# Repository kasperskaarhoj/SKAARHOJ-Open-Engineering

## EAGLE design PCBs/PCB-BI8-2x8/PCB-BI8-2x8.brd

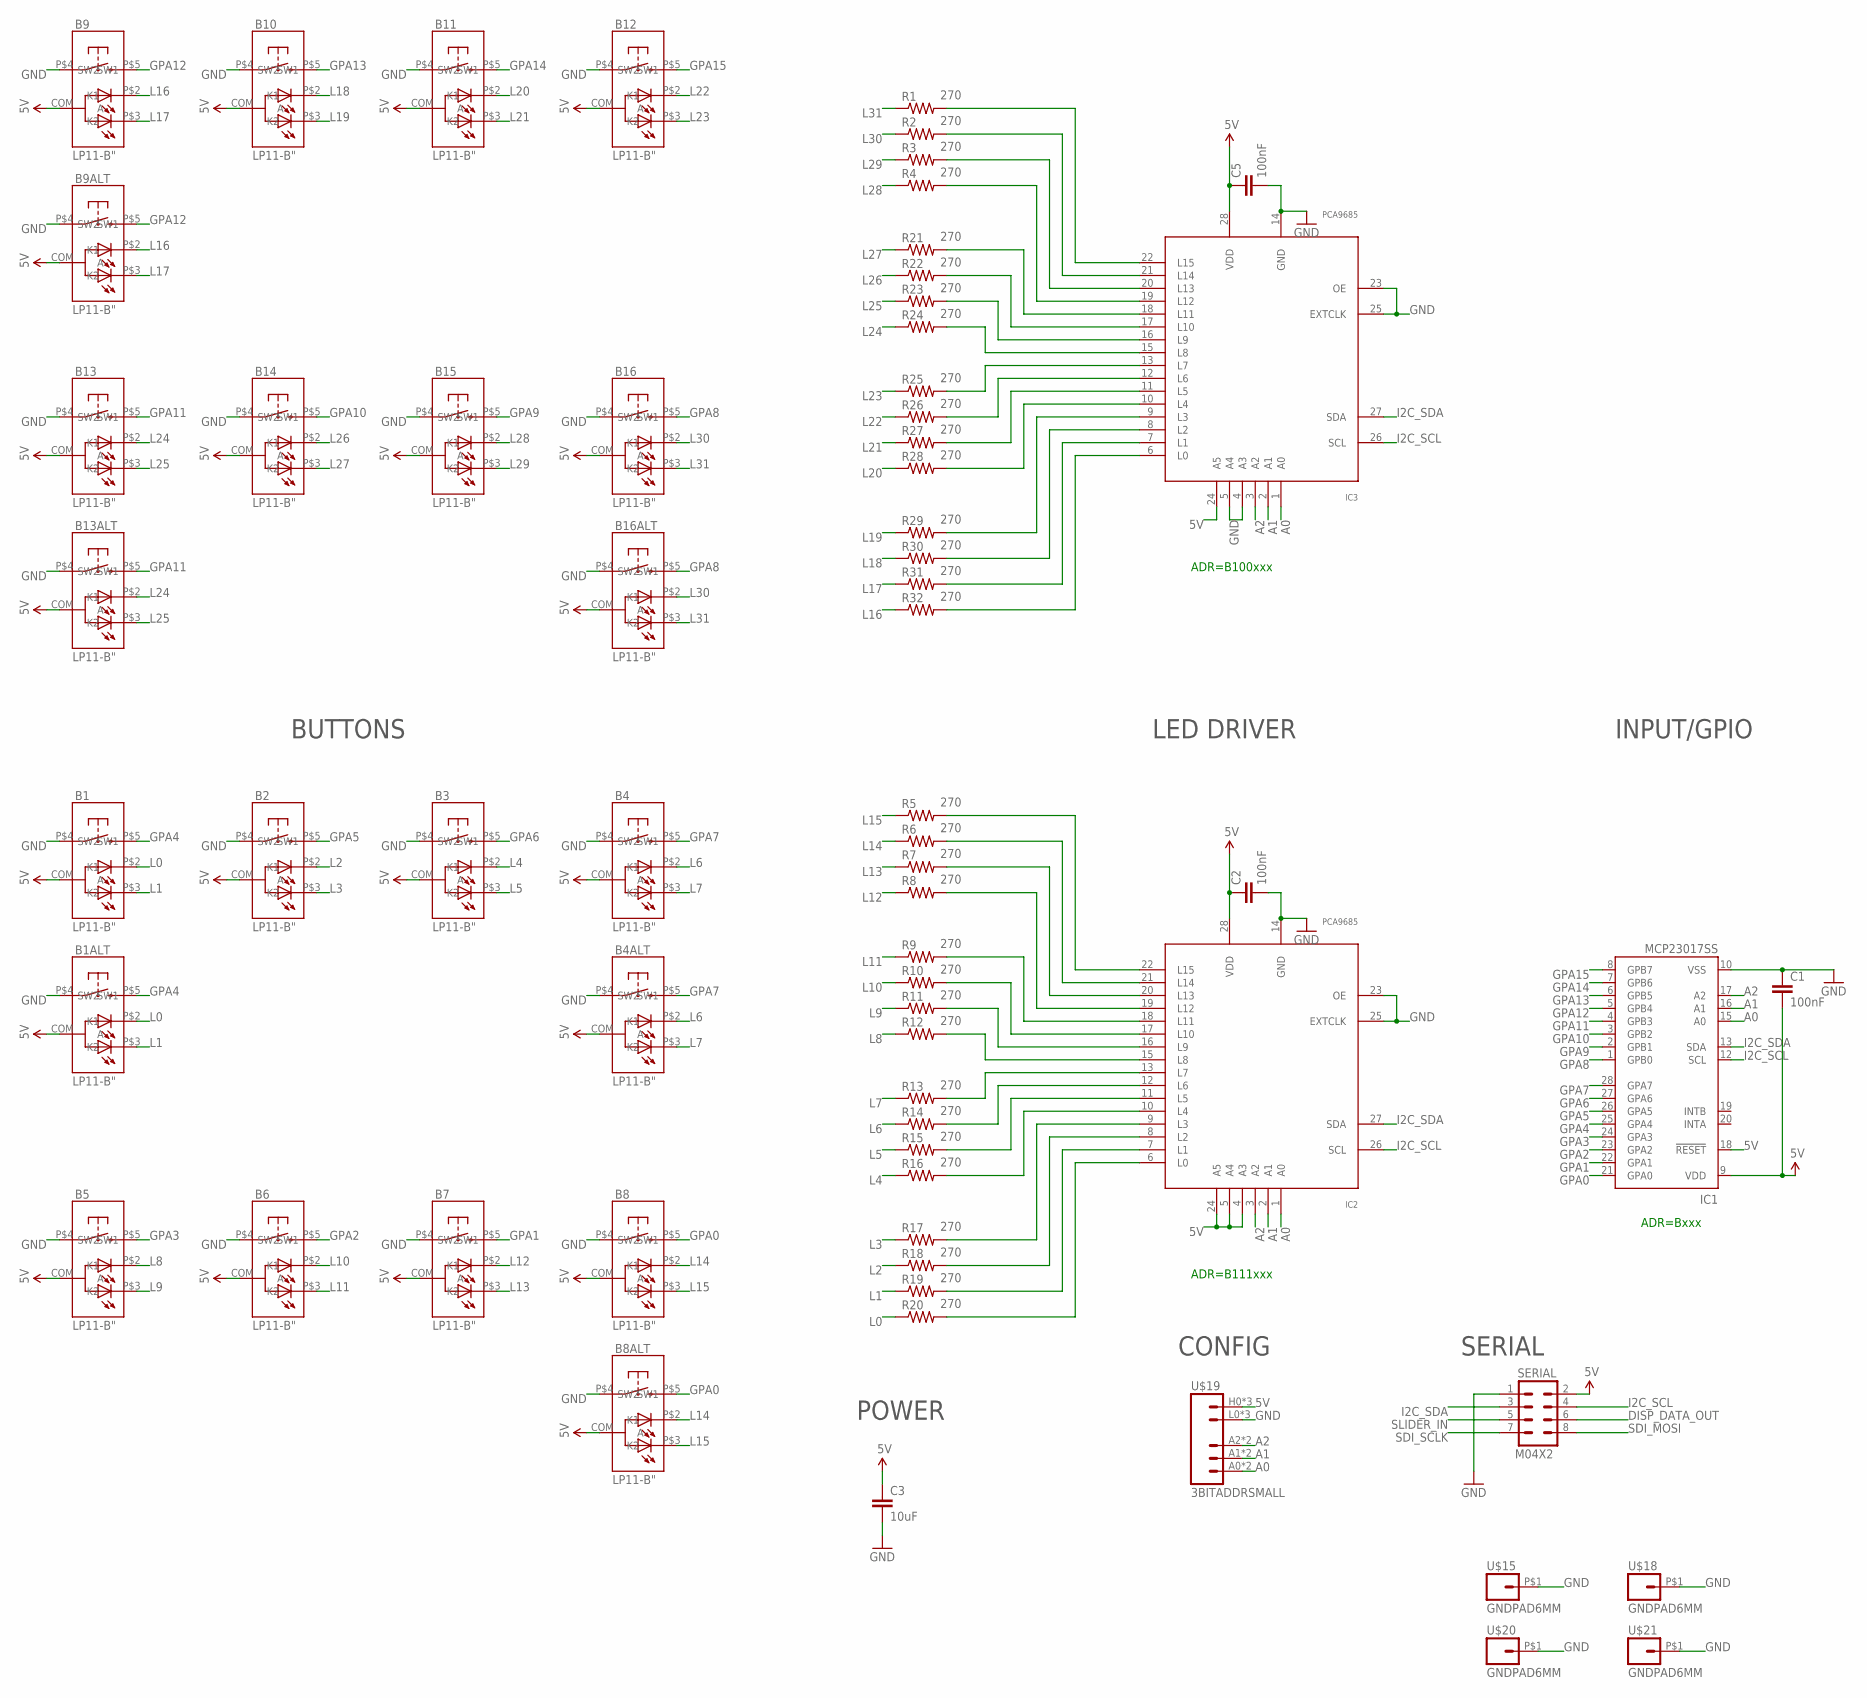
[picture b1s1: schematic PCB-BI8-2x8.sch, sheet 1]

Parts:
B1, B1ALT, B2, B3, B4, B4ALT, B5, B6, B7, B8, B8ALT, B9, B9ALT, B10, B11, B12, B13, B13ALT, B14, B15, B16, B16ALT: LP11-B"; LP11
C1, C2, C5: 100nF; 0603-CAP
C3: 10uF; 0805
IC1: MCP23017SS; SSOP28; MPN MCP23017-E/SS
IC2, IC3: PCA9685; TSSOP28
R1, R2, R3, R4, R5, R6, R7, R8, R9, R10, R11, R12, R13, R14, R15, R16, R17, R18, R19, R20, R21, R22, R23, R24, R25, R26, R27, R28, R29, R30, R31, R32: 270; 0603-RES
SERIAL: M04X2; 2X4
U$15, U$18, U$20, U$21: GNDPAD6MM; 3.2MMPAD6MM
U$19: 3BITADDRSMALL; 3BITADDR_SMALL

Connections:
5V: B1.COM (A), B1ALT.COM (A), B2.COM (A), B3.COM (A), B4.COM (A), B4ALT.COM (A), B5.COM (A), B6.COM (A), B7.COM (A), B8.COM (A), B8ALT.COM (A), B9.COM (A), B9ALT.COM (A), B10.COM (A), B11.COM (A), B12.COM (A), B13.COM (A), B13ALT.COM (A), B14.COM (A), B15.COM (A), B16.COM (A), B16ALT.COM (A), C1.2, C2.1, C3.1, C5.1, IC1.9 (VDD), IC1.18 (!RESET), IC2.4 (A3), IC2.5 (A4), IC2.24 (A5), IC2.28 (VDD), IC3.24 (A5), IC3.28 (VDD), SERIAL.2, U$19.H0 (VCC), U$19.H1 (VCC), U$19.H2 (VCC)
A0: IC1.15 (A0), IC2.1 (A0), IC3.1 (A0), U$19.A0, U$19.AS0 (A0)
A1: IC1.16 (A1), IC2.2 (A1), IC3.2 (A1), U$19.A1, U$19.AS1 (A1)
A2: IC1.17 (A2), IC2.3 (A2), IC3.3 (A2), U$19.A2, U$19.AS2 (A2)
DISP_DATA_OUT: SERIAL.6
GND: B1.P$4 (SW1), B1ALT.P$4 (SW1), B2.P$4 (SW1), B3.P$4 (SW1), B4.P$4 (SW1), B4ALT.P$4 (SW1), B5.P$4 (SW1), B6.P$4 (SW1), B7.P$4 (SW1), B8.P$4 (SW1), B8ALT.P$4 (SW1), B9.P$4 (SW1), B9ALT.P$4 (SW1), B10.P$4 (SW1), B11.P$4 (SW1), B12.P$4 (SW1), B13.P$4 (SW1), B13ALT.P$4 (SW1), B14.P$4 (SW1), B15.P$4 (SW1), B16.P$4 (SW1), B16ALT.P$4 (SW1), C1.1, C2.2, C3.2, C5.2, IC1.10 (VSS), IC2.14 (GND), IC2.23 (OE), IC2.25 (EXTCLK), IC3.4 (A3), IC3.5 (A4), IC3.14 (GND), IC3.23 (OE), IC3.25 (EXTCLK), SERIAL.1, U$15.P$1, U$18.P$1, U$19.L0 (GND), U$19.L1 (GND), U$19.L2 (GND), U$20.P$1, U$21.P$1
GPA0: B8.P$5 (SW2), B8ALT.P$5 (SW2), IC1.21 (GPA0)
GPA1: B7.P$5 (SW2), IC1.22 (GPA1)
GPA2: B6.P$5 (SW2), IC1.23 (GPA2)
GPA3: B5.P$5 (SW2), IC1.24 (GPA3)
GPA4: B1.P$5 (SW2), B1ALT.P$5 (SW2), IC1.25 (GPA4)
GPA5: B2.P$5 (SW2), IC1.26 (GPA5)
GPA6: B3.P$5 (SW2), IC1.27 (GPA6)
GPA7: B4.P$5 (SW2), B4ALT.P$5 (SW2), IC1.28 (GPA7)
GPA8: B16.P$5 (SW2), B16ALT.P$5 (SW2), IC1.1 (GPB0)
GPA9: B15.P$5 (SW2), IC1.2 (GPB1)
GPA10: B14.P$5 (SW2), IC1.3 (GPB2)
GPA11: B13.P$5 (SW2), B13ALT.P$5 (SW2), IC1.4 (GPB3)
GPA12: B9.P$5 (SW2), B9ALT.P$5 (SW2), IC1.5 (GPB4)
GPA13: B10.P$5 (SW2), IC1.6 (GPB5)
GPA14: B11.P$5 (SW2), IC1.7 (GPB6)
GPA15: B12.P$5 (SW2), IC1.8 (GPB7)
I2C_SCL: IC1.12 (SCL), IC2.26 (SCL), IC3.26 (SCL), SERIAL.4
I2C_SDA: IC1.13 (SDA), IC2.27 (SDA), IC3.27 (SDA), SERIAL.3
L0: B1.P$2 (K1), B1ALT.P$2 (K1), R20.1
L1: B1.P$3 (K2), B1ALT.P$3 (K2), R19.1
L2: B2.P$2 (K1), R18.1
L3: B2.P$3 (K2), R17.1
L4: B3.P$2 (K1), R16.1
L5: B3.P$3 (K2), R15.1
L6: B4.P$2 (K1), B4ALT.P$2 (K1), R14.1
L7: B4.P$3 (K2), B4ALT.P$3 (K2), R13.1
L8: B5.P$2 (K1), R12.1
L9: B5.P$3 (K2), R11.1
L10: B6.P$2 (K1), R10.1
L11: B6.P$3 (K2), R9.1
L12: B7.P$2 (K1), R8.1
L13: B7.P$3 (K2), R7.1
L14: B8.P$2 (K1), B8ALT.P$2 (K1), R6.1
L15: B8.P$3 (K2), B8ALT.P$3 (K2), R5.1
L16: B9.P$2 (K1), B9ALT.P$2 (K1), R32.1
L17: B9.P$3 (K2), B9ALT.P$3 (K2), R31.1
L18: B10.P$2 (K1), R30.1
L19: B10.P$3 (K2), R29.1
L20: B11.P$2 (K1), R28.1
L21: B11.P$3 (K2), R27.1
L22: B12.P$2 (K1), R26.1
L23: B12.P$3 (K2), R25.1
L24: B13.P$2 (K1), B13ALT.P$2 (K1), R24.1
L25: B13.P$3 (K2), B13ALT.P$3 (K2), R23.1
L26: B14.P$2 (K1), R22.1
L27: B14.P$3 (K2), R21.1
L28: B15.P$2 (K1), R4.1
L29: B15.P$3 (K2), R3.1
L30: B16.P$2 (K1), B16ALT.P$2 (K1), R2.1
L31: B16.P$3 (K2), B16ALT.P$3 (K2), R1.1
unnamed: IC3.13 (L7), R25.2
unnamed: IC3.12 (L6), R26.2
unnamed: IC3.11 (L5), R27.2
unnamed: IC2.13 (L7), R13.2
unnamed: IC2.12 (L6), R14.2
unnamed: IC3.10 (L4), R28.2
unnamed: IC2.11 (L5), R15.2
unnamed: IC3.9 (L3), R29.2
unnamed: IC2.10 (L4), R16.2
unnamed: IC2.9 (L3), R17.2
unnamed: IC2.8 (L2), R18.2
unnamed: IC2.7 (L1), R19.2
unnamed: IC3.8 (L2), R30.2
unnamed: IC3.7 (L1), R31.2
unnamed: IC3.6 (L0), R32.2
unnamed: IC3.15 (L8), R24.2
unnamed: IC3.16 (L9), R23.2
unnamed: IC3.17 (L10), R22.2
unnamed: IC2.6 (L0), R20.2
unnamed: IC2.15 (L8), R12.2
unnamed: IC2.16 (L9), R11.2
unnamed: IC2.17 (L10), R10.2
unnamed: IC2.18 (L11), R9.2
unnamed: IC2.19 (L12), R8.2
unnamed: IC2.20 (L13), R7.2
unnamed: IC2.21 (L14), R6.2
unnamed: IC2.22 (L15), R5.2
unnamed: IC3.18 (L11), R21.2
unnamed: IC3.19 (L12), R4.2
unnamed: IC3.20 (L13), R3.2
unnamed: IC3.21 (L14), R2.2
unnamed: IC3.22 (L15), R1.2
SDI_MOSI: SERIAL.8
SDI_SCLK: SERIAL.7
SLIDER_IN: SERIAL.5

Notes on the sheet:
ADR=B111xxx
ADR=Bxxx
BUTTONS
LED DRIVER
INPUT/GPIO
POWER
SERIAL
CONFIG
ADR=B100xxx

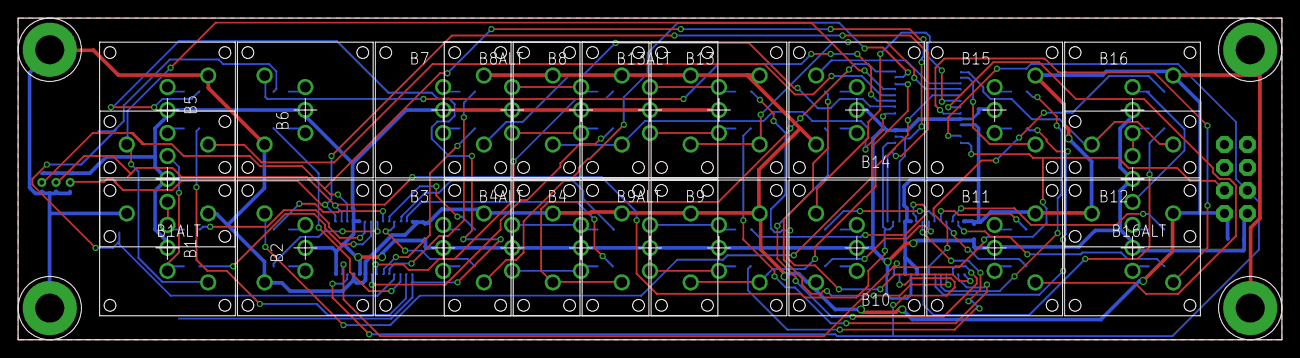
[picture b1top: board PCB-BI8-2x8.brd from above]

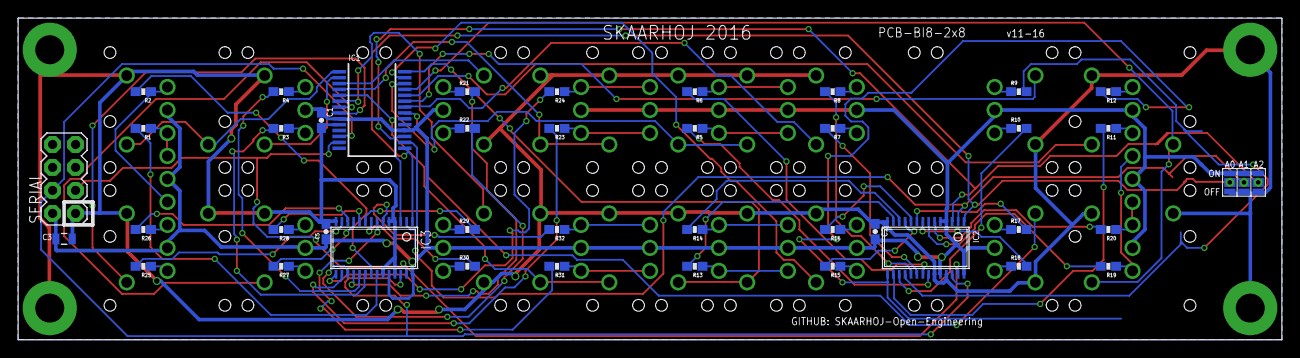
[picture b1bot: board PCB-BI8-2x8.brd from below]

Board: 2 copper layers, 139.7 x 35.6 mm, 67 parts (41 on the bottom side), 87 nets.

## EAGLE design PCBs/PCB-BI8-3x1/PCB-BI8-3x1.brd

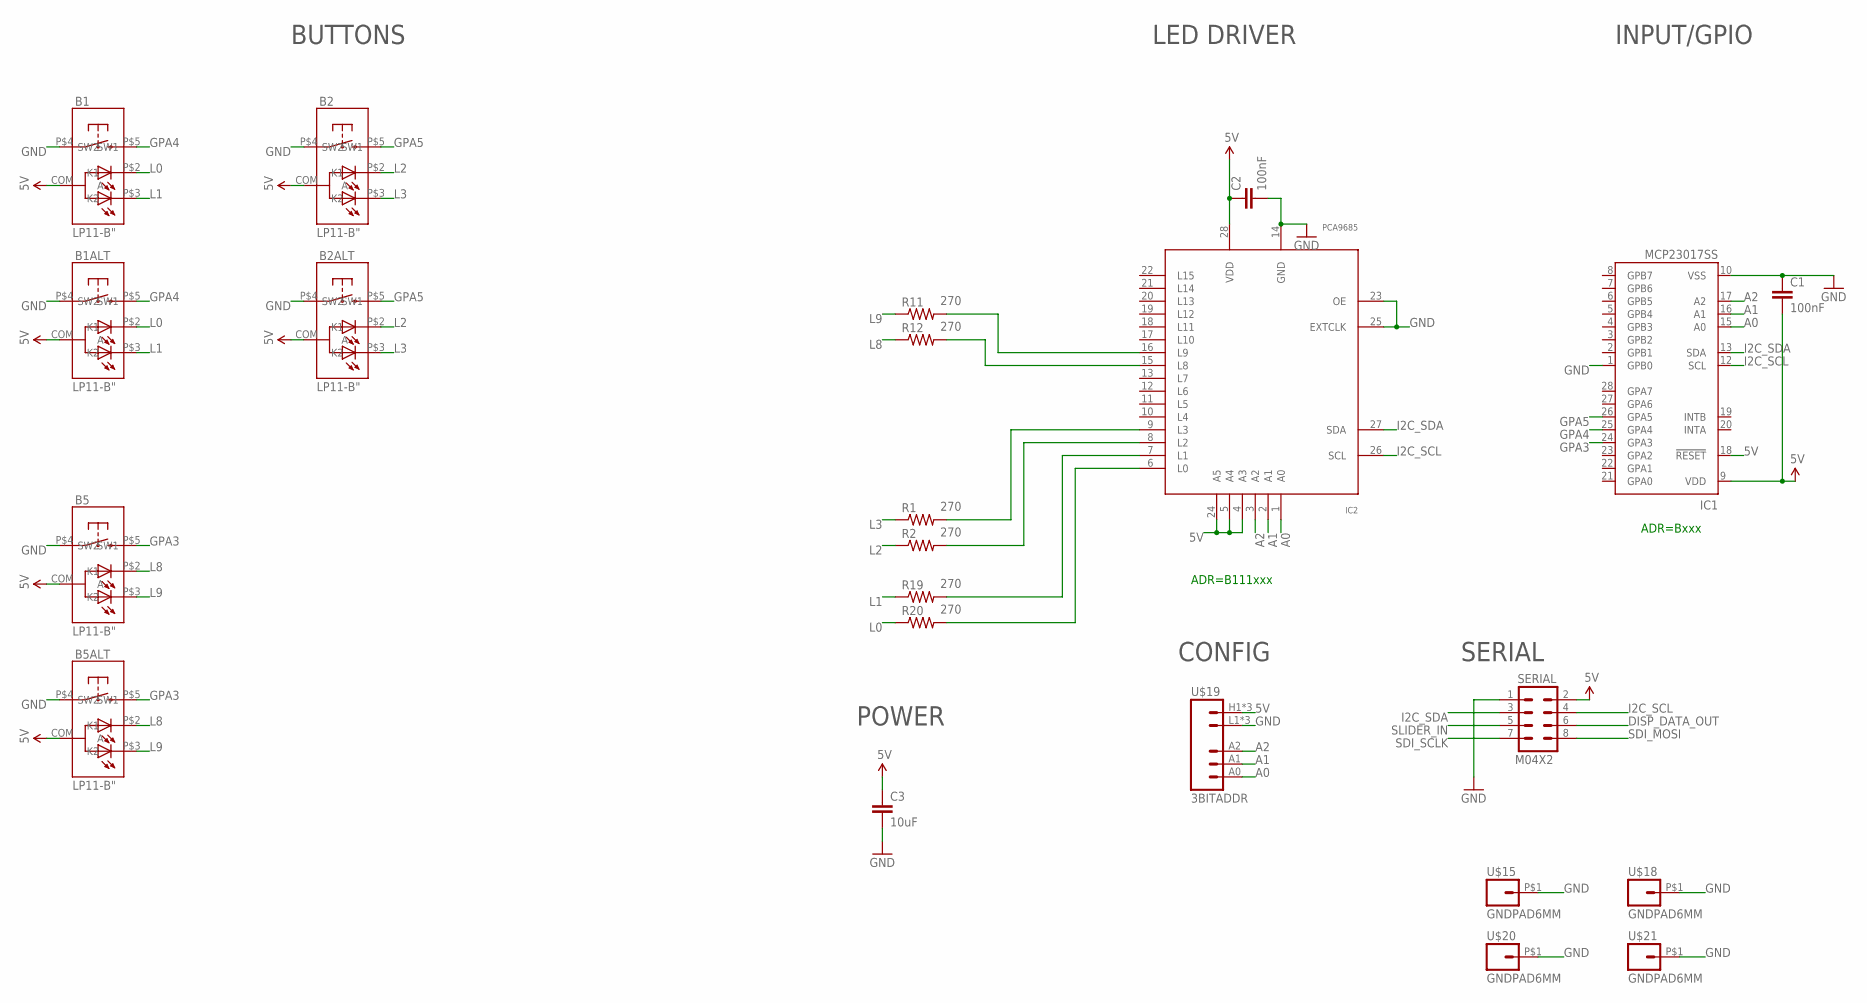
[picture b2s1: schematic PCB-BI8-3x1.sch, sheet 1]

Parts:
B1, B1ALT, B2, B2ALT, B5, B5ALT: LP11-B"; LP11
C1, C2: 100nF; 0603-CAP
C3: 10uF; 0805
IC1: MCP23017SS; SSOP28; MPN MCP23017-E/SS
IC2: PCA9685; TSSOP28
R1, R2, R11, R12, R19, R20: 270; 0603-RES
SERIAL: M04X2; 2X4
U$15, U$18, U$20, U$21: GNDPAD6MM; 3.2MMPAD6MM
U$19: 3BITADDR

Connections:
5V: B1.COM (A), B1ALT.COM (A), B2.COM (A), B2ALT.COM (A), B5.COM (A), B5ALT.COM (A), C1.2, C2.1, C3.1, IC1.9 (VDD), IC1.18 (!RESET), IC2.4 (A3), IC2.5 (A4), IC2.24 (A5), IC2.28 (VDD), SERIAL.2, U$19.H1 (VCC), U$19.H2 (VCC), U$19.H3 (VCC)
A0: IC1.15 (A0), IC2.1 (A0), U$19.A0
A1: IC1.16 (A1), IC2.2 (A1), U$19.A1
A2: IC1.17 (A2), IC2.3 (A2), U$19.A2
DISP_DATA_OUT: SERIAL.6
GND: B1.P$4 (SW1), B1ALT.P$4 (SW1), B2.P$4 (SW1), B2ALT.P$4 (SW1), B5.P$4 (SW1), B5ALT.P$4 (SW1), C1.1, C2.2, C3.2, IC1.1 (GPB0), IC1.10 (VSS), IC2.14 (GND), IC2.23 (OE), IC2.25 (EXTCLK), SERIAL.1, U$15.P$1, U$18.P$1, U$19.L1 (GND), U$19.L2 (GND), U$19.L3 (GND), U$20.P$1, U$21.P$1
GPA3: B5.P$5 (SW2), B5ALT.P$5 (SW2), IC1.24 (GPA3)
GPA4: B1.P$5 (SW2), B1ALT.P$5 (SW2), IC1.25 (GPA4)
GPA5: B2.P$5 (SW2), B2ALT.P$5 (SW2), IC1.26 (GPA5)
I2C_SCL: IC1.12 (SCL), IC2.26 (SCL), SERIAL.4
I2C_SDA: IC1.13 (SDA), IC2.27 (SDA), SERIAL.3
L0: B1.P$2 (K1), B1ALT.P$2 (K1), R20.1
L1: B1.P$3 (K2), B1ALT.P$3 (K2), R19.1
L2: B2.P$2 (K1), B2ALT.P$2 (K1), R2.1
L3: B2.P$3 (K2), B2ALT.P$3 (K2), R1.1
L8: B5.P$2 (K1), B5ALT.P$2 (K1), R12.1
L9: B5.P$3 (K2), B5ALT.P$3 (K2), R11.1
unnamed: IC2.8 (L2), R2.2
unnamed: IC2.9 (L3), R1.2
unnamed: IC2.7 (L1), R19.2
unnamed: IC2.6 (L0), R20.2
unnamed: IC2.15 (L8), R12.2
unnamed: IC2.16 (L9), R11.2
SDI_MOSI: SERIAL.8
SDI_SCLK: SERIAL.7
SLIDER_IN: SERIAL.5

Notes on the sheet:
ADR=B111xxx
ADR=Bxxx
BUTTONS
LED DRIVER
INPUT/GPIO
POWER
SERIAL
CONFIG

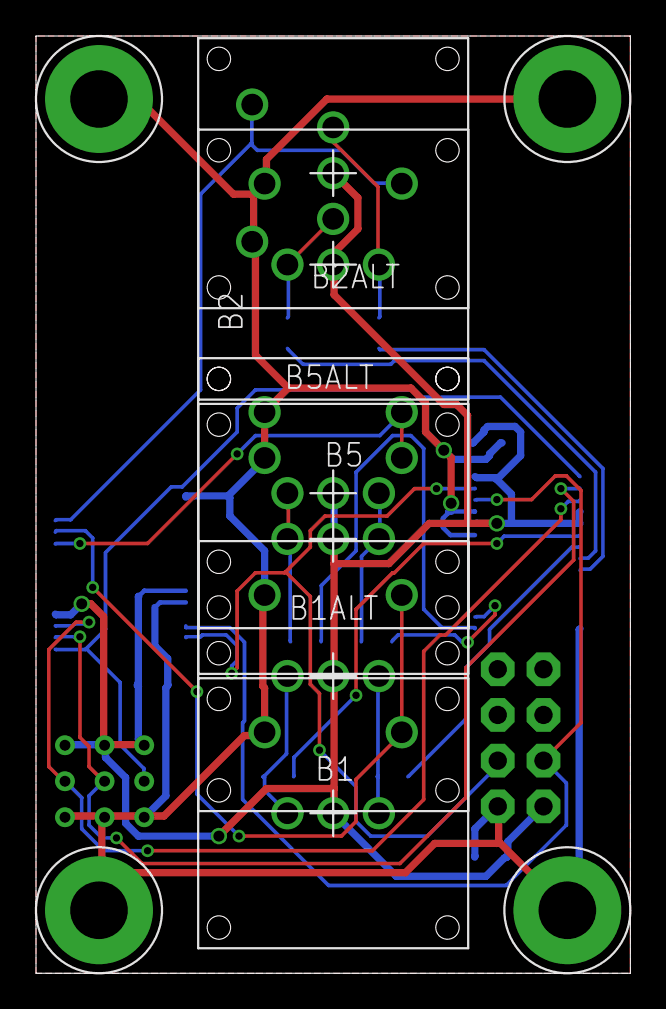
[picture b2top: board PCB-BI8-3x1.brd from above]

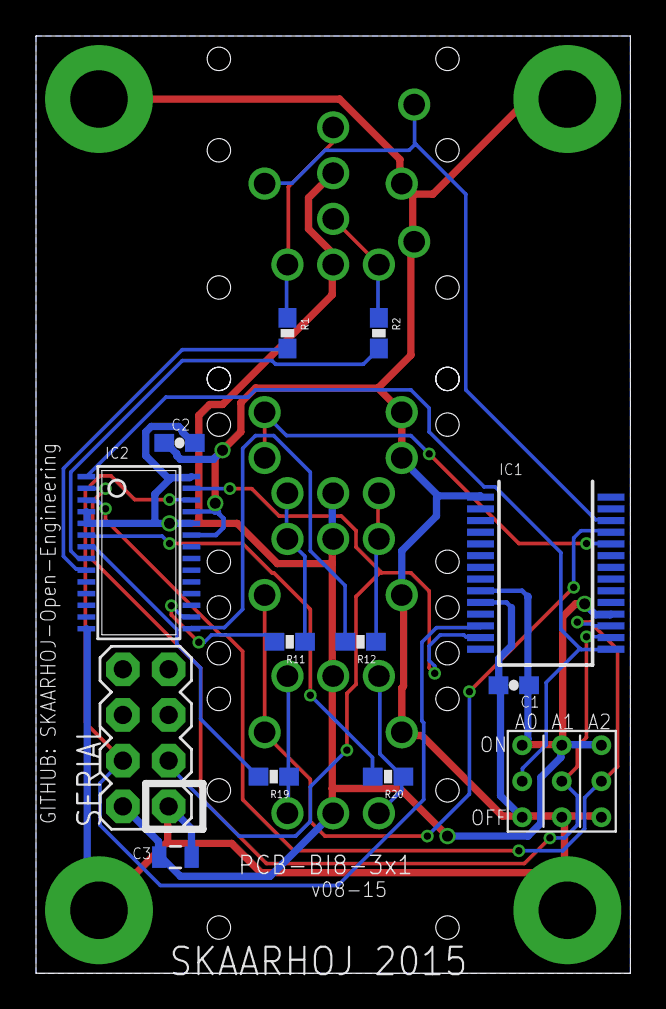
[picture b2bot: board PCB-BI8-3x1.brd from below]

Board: 2 copper layers, 33.0 x 52.1 mm, 23 parts (13 on the bottom side), 22 nets.

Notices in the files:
parts and their libraries:
SparkFun: Licensing: CC v3.0 Share-Alike You are welcome to use this library for commercial purposes.
